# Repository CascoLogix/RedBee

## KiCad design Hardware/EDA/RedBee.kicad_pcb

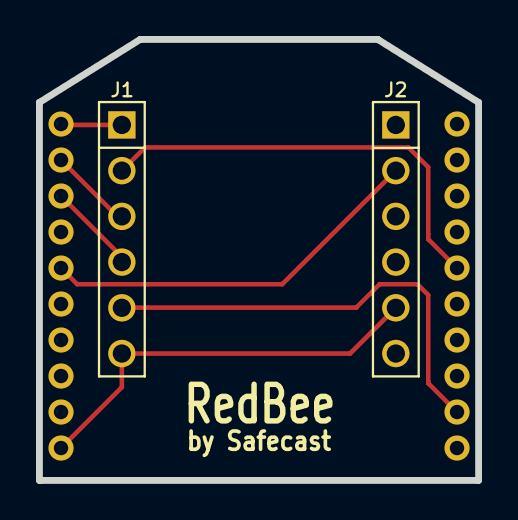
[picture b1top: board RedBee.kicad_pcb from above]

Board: 2 copper layers, 24.4 x 24.5 mm, 3 parts (1 on the bottom side), 7 nets.

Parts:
J1, J2: HEADER_F_2.54MM_1R6P_ST_AU_PTH
P1: XBee Pins Footprint; HEADER_XBEE

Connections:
CTS_HEADER: J1.2, P1.16
GND: J1.6, J2.5, P1.10
RESET: J2.2, P1.5
RTS_HEADER: J1.5, P1.12
RXD_HEADER: J1.4, P1.3
TXD_HEADER: J1.3, P1.2
VDD: J1.1, P1.1

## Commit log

2016-04-09 First commit.
2016-04-14 Changed board outline to conform to standard Digi XBee outline. Moved text on silkscreen. Swapped CTS and RTS to correct for DTE perspective. Updated schematic.
2016-04-14 Added ignore file
2016-05-12 Added photos, library footprint archive and updated schematic with properties in header component schematic decals.
2016-05-15 Cleaned up files
